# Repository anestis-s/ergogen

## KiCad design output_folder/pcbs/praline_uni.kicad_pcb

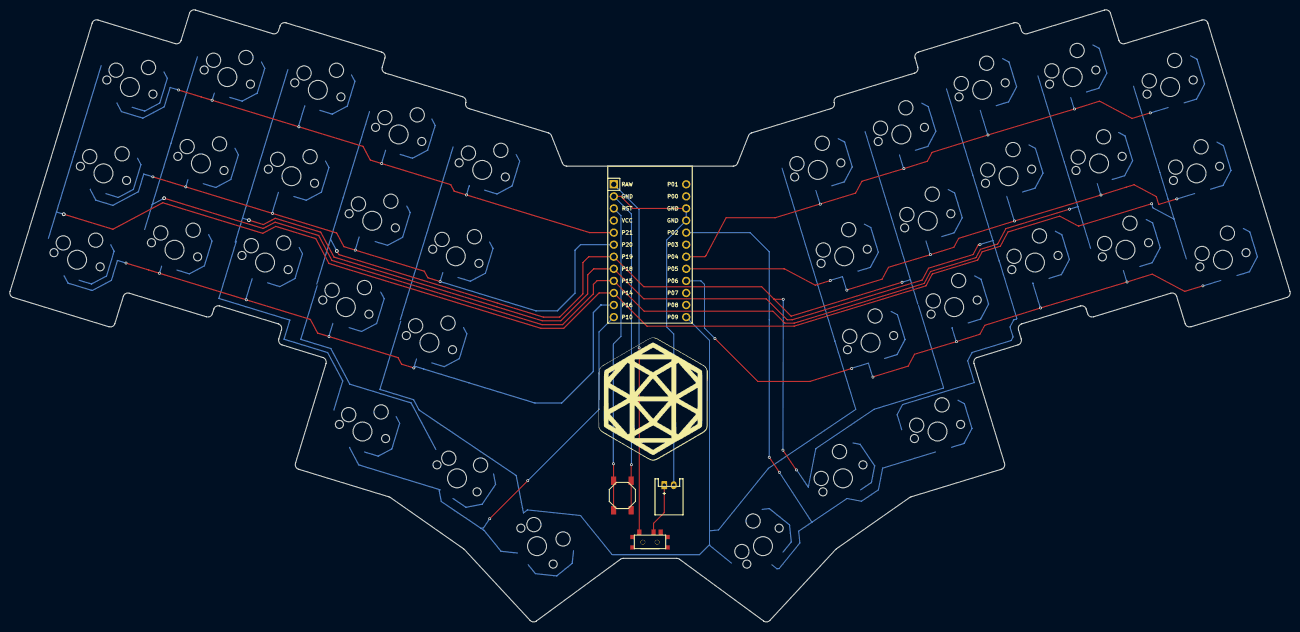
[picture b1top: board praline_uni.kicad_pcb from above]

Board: 2 copper layers, 269.4 x 128.8 mm, 76 parts (0 on the bottom side), 53 nets.

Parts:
B1: SW_TACT_ALPS_SKQGABE010
D1, D2, D3, D4, D5, D6, D7, D8, D9, D10, D11, D12, D13, D14, D15, D16, D17, D18, D19, D20, D21, D22, D23, D24, D25, D26, D27, D28, D29, D30, D31, D32, D33, D34, D35, D36: ComboDiode
JST1: JST_PH_S2B-PH-K_02x2.00mm_Angled
MCU1: ProMicro
S1, S2, S3, S4, S5, S6, S7, S8, S9, S10, S11, S12, S13, S14, S15, S16, S17, S18, S19, S20, S21, S22, S23, S24, S25, S26, S27, S28, S29, S30, S31, S32, S33, S34, S35, S36: MX
T1: SPDT_C128955

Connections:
GND: B1.1, JST1.2, MCU1.2, MCU1.15, MCU1.16
P2: D34.1, D35.1, D36.1, MCU1.17
P4: D21.1, D24.1, D27.1, D30.1, D33.1, MCU1.19
P5: D20.1, D23.1, D26.1, D29.1, D32.1, MCU1.20
P6: D19.1, D22.1, D25.1, D28.1, D31.1, MCU1.21
P9: MCU1.24, S13.1, S14.1, S15.1, S18.1, S31.1, S32.1, S33.1, S36.1
P10: D16.1, D17.1, D18.1, MCU1.12
P14: MCU1.10, S1.1, S2.1, S3.1, S19.1, S20.1, S21.1
P15: MCU1.9, S4.1, S5.1, S6.1, S22.1, S23.1, S24.1
P16: D1.1, D4.1, D7.1, D10.1, D13.1, MCU1.11
P18: MCU1.8, S7.1, S8.1, S9.1, S16.1, S25.1, S26.1, S27.1, S34.1
P19: MCU1.7, S10.1, S11.1, S12.1, S17.1, S28.1, S29.1, S30.1, S35.1
P20: D2.1, D5.1, D8.1, D11.1, D14.1, MCU1.6
P21: D3.1, D6.1, D9.1, D12.1, D15.1, MCU1.5
POS: JST1.1, T1.2
RAW: MCU1.1, T1.1
RST: B1.2, MCU1.3
far_thumb: D18.2, S18.2
home_thumb: D17.2, S17.2
index_bottom: D10.2, S10.2
index_home: D11.2, S11.2
index_top: D12.2, S12.2
inner_bottom: D13.2, S13.2
inner_home: D14.2, S14.2
inner_top: D15.2, S15.2
middle_bottom: D7.2, S7.2
middle_home: D8.2, S8.2
middle_top: D9.2, S9.2
mirror_far_thumb: D36.2, S36.2
mirror_home_thumb: D35.2, S35.2
mirror_index_bottom: D28.2, S28.2
mirror_index_home: D29.2, S29.2
mirror_index_top: D30.2, S30.2
mirror_inner_bottom: D31.2, S31.2
mirror_inner_home: D32.2, S32.2
mirror_inner_top: D33.2, S33.2
mirror_middle_bottom: D25.2, S25.2
mirror_middle_home: D26.2, S26.2
mirror_middle_top: D27.2, S27.2
mirror_near_thumb: D34.2, S34.2
mirror_pinky_bottom: D19.2, S19.2
mirror_pinky_home: D20.2, S20.2
mirror_pinky_top: D21.2, S21.2
mirror_ring_bottom: D22.2, S22.2
mirror_ring_home: D23.2, S23.2
mirror_ring_top: D24.2, S24.2
near_thumb: D16.2, S16.2
pinky_bottom: D1.2, S1.2
pinky_home: D2.2, S2.2
pinky_top: D3.2, S3.2
ring_bottom: D4.2, S4.2
ring_home: D5.2, S5.2
ring_top: D6.2, S6.2

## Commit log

2023-04-06 update footprints
2023-04-06 add ergogen praline yamls
2023-08-05 add unibody yaml
2023-09-12 update outlines
2023-09-13 change distances
2023-09-15 correct mirror row
2023-09-15 rearrange nets
2023-09-15 routed pcb
2023-09-20 add routed pcbs
